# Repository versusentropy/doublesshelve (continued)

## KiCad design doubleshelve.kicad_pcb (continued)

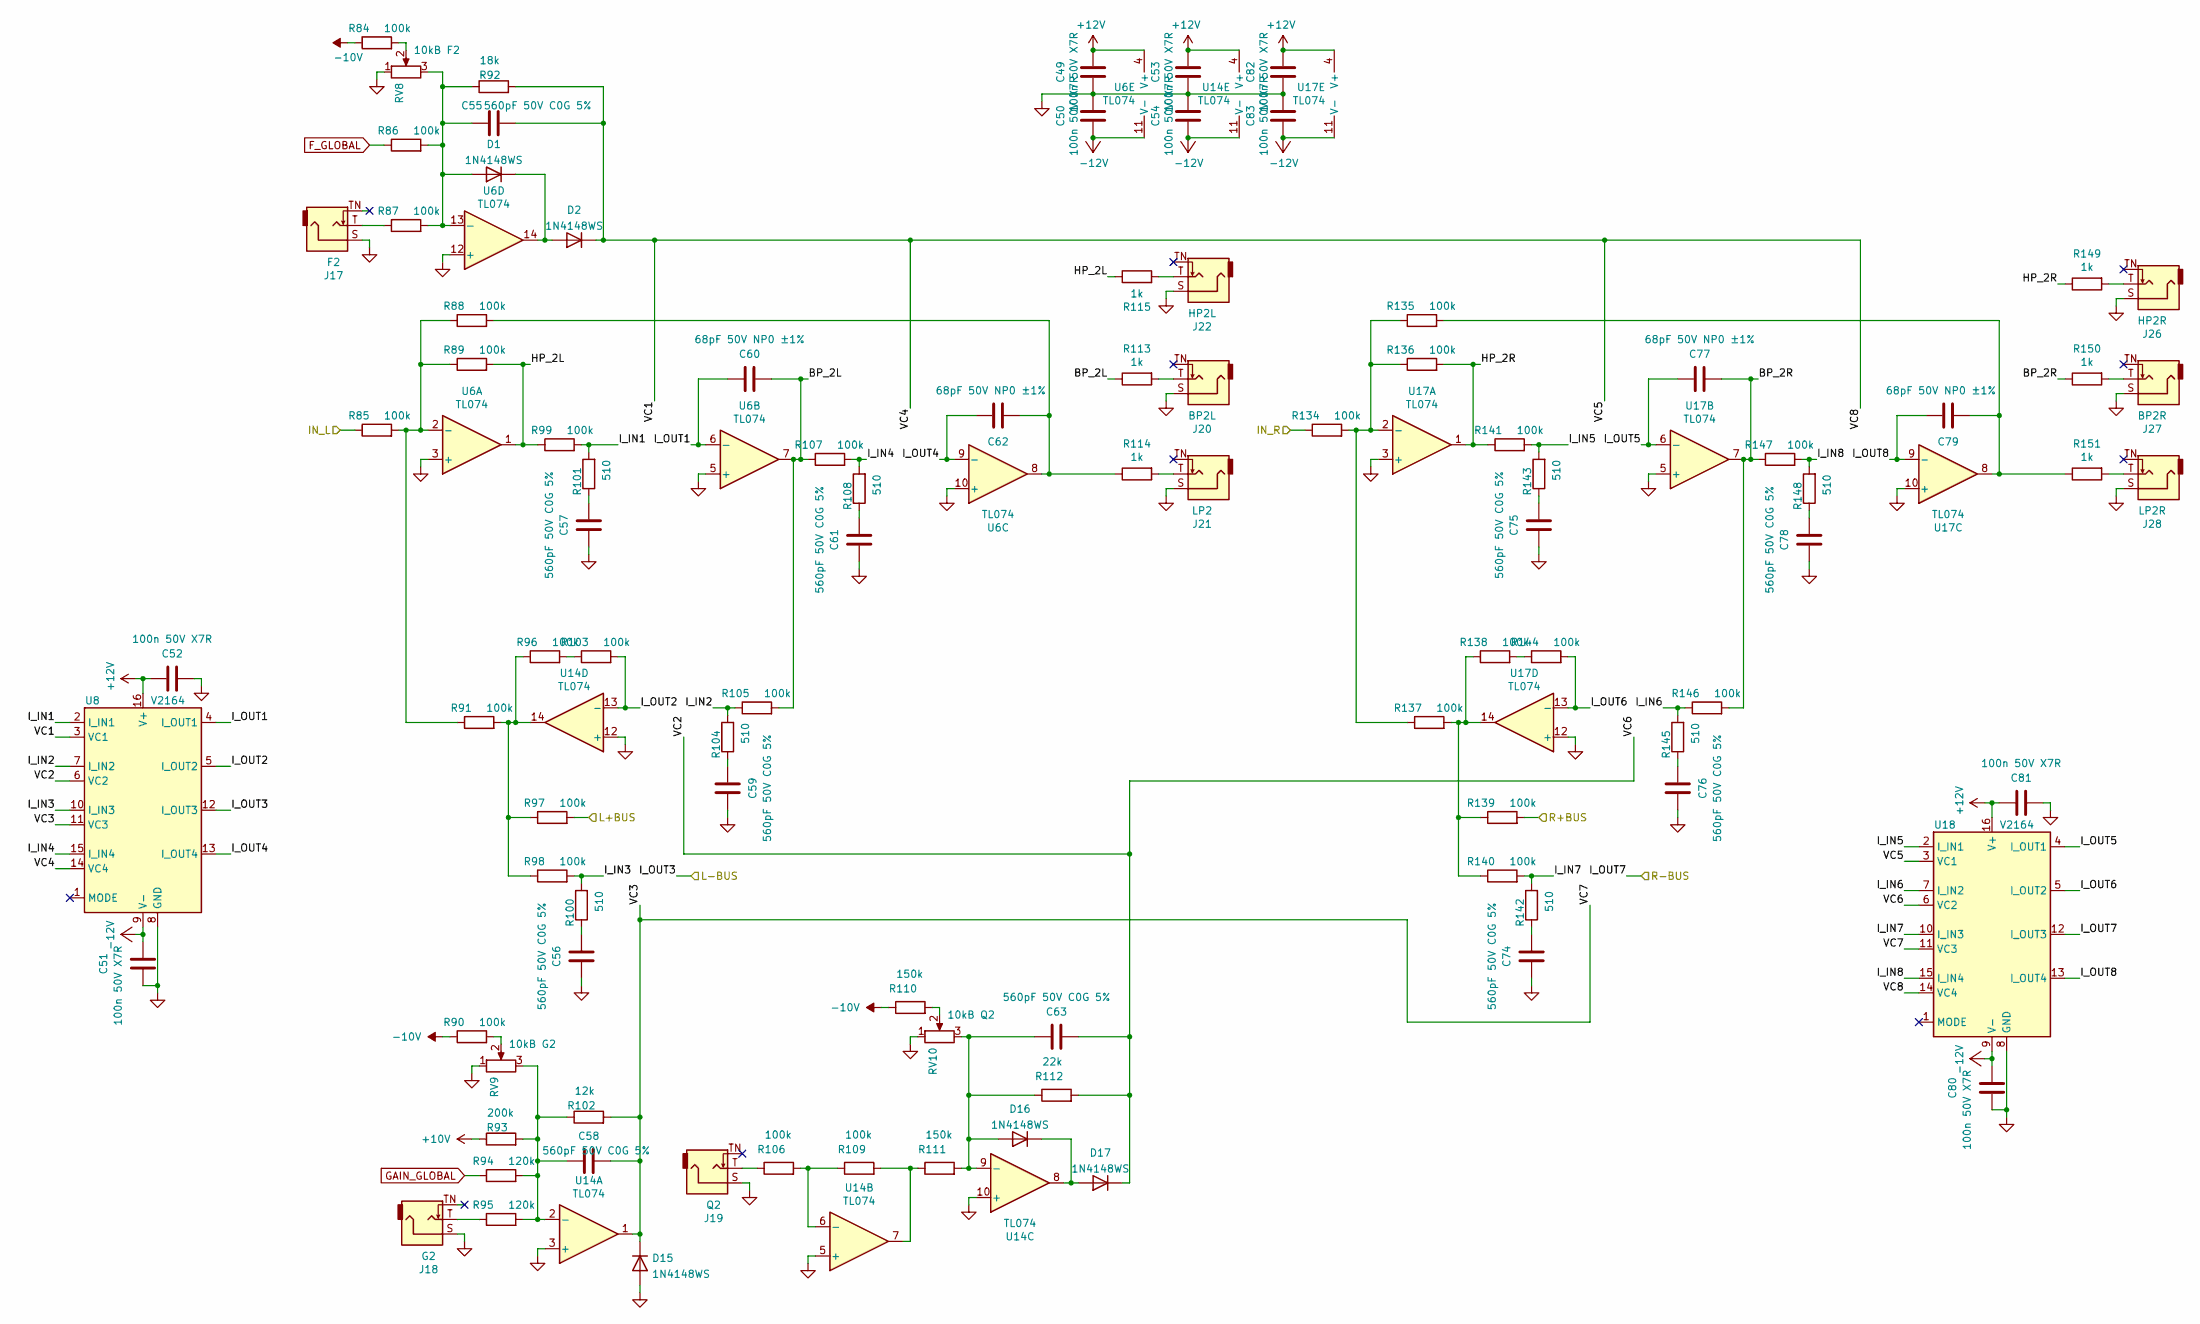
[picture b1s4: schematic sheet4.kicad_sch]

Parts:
C49, C50, C51, C52, C53, C54, C80, C81, C82, C83: 100n 50V X7R; C_0402_1005Metric; LCSC C307331
C55, C56, C57, C58, C59, C61, C63, C74, C75, C76, C78: 560pF 50V C0G 5%; C_0603_1608Metric; LCSC C97881
C60, C62, C77, C79: 68pF 50V NP0 ±1%; C_0402_1005Metric; LCSC C5182453
D1, D2, D15, D16, D17: 1N4148WS; D_SOD-323; LCSC C2128
J17: F2; Jack_3.5mm_QingPu_WQP-PJ398SM_Vertical_CircularHolesSMALL
J18: G2; Jack_3.5mm_QingPu_WQP-PJ398SM_Vertical_CircularHolesSMALL
J19: Q2; Jack_3.5mm_QingPu_WQP-PJ398SM_Vertical_CircularHolesSMALL
J20: BP2L; Jack_3.5mm_QingPu_WQP-PJ398SM_Vertical_CircularHolesSMALL
J21: LP2; Jack_3.5mm_QingPu_WQP-PJ398SM_Vertical_CircularHolesSMALL
J22: HP2L; Jack_3.5mm_QingPu_WQP-PJ398SM_Vertical_CircularHolesSMALL
J26: HP2R; Jack_3.5mm_QingPu_WQP-PJ398SM_Vertical_CircularHolesSMALL
J27: BP2R; Jack_3.5mm_QingPu_WQP-PJ398SM_Vertical_CircularHolesSMALL
J28: LP2R; Jack_3.5mm_QingPu_WQP-PJ398SM_Vertical_CircularHolesSMALL
R84, R85, R86, R87, R88, R89, R90, R91, R96, R97, R98, R99, R103, R105, R106, R107, R109, R134, R135, R136, R137, R138, R139, R140, R141, R144, R146, R147: 100k; R_0402_1005Metric; LCSC C319963
R92: 18k; R_0402_1005Metric
R93: 200k; R_0402_1005Metric
R94, R95: 120k; R_0402_1005Metric
R100, R101, R104, R108, R142, R143, R145, R148: 510; R_0402_1005Metric
R102: 12k; R_0402_1005Metric
R110, R111: 150k; R_0402_1005Metric
R112: 22k; R_0402_1005Metric
R113, R114, R115, R149, R150, R151: 1k; R_0603_1608Metric; LCSC C394536
RV8: 10kB F2; RD901F-ALPHA-POT
RV9: 10kB G2; RD901F-ALPHA-POT
RV10: 10kB Q2; RD901F-ALPHA-POT
U6, U14, U17: TL074; SOIC-14_3.9x8.7mm_P1.27mm; LCSC C96507
U8, U18: V2164; SOIC-16_3.9x9.9mm_P1.27mm

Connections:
+10V: R93.1; also elsewhere on the board
+12V: C49.2, C52.2, C53.2, C81.2, C82.2, U6.4 (V+), U8.16 (V+), U14.4 (V+), U17.4 (V+), U18.16 (V+); also elsewhere on the board
-10V: R84.1, R90.1, R110.1; also elsewhere on the board
-12V: C50.1, C51.2, C54.1, C80.2, C83.1, U6.11 (V-), U8.9 (V-), U14.11 (V-), U17.11 (V-), U18.9 (V-); also elsewhere on the board
/sheet1/IN_L: R85.1; also elsewhere on the board
/sheet1/IN_R: R134.1; also elsewhere on the board
/sheet1/L+BUS: R97.2; also elsewhere on the board
/sheet1/R+BUS: R139.2; also elsewhere on the board
/sheet3/I_OUT3: U8.12 (I_OUT3); also elsewhere on the board
/sheet3/I_OUT7: U18.12 (I_OUT3); also elsewhere on the board
/sheet4/BP_2L: C60.1, R105.2, R107.1, R113.1, U6.7
/sheet4/BP_2R: C77.1, R146.2, R147.1, R150.1, U17.7
/sheet4/HP_2L: R89.2, R99.1, R115.1, U6.1
/sheet4/HP_2R: R136.2, R141.1, R149.1, U17.1
/sheet4/I_IN1: R99.2, R101.2, U8.2 (I_IN1)
/sheet4/I_IN2: R104.2, R105.1, U8.7 (I_IN2)
/sheet4/I_IN3: R98.2, R100.2, U8.10 (I_IN3)
/sheet4/I_IN4: R107.2, R108.2, U8.15 (I_IN4)
/sheet4/I_IN5: R141.2, R143.2, U18.2 (I_IN1)
/sheet4/I_IN6: R145.2, R146.1, U18.7 (I_IN2)
/sheet4/I_IN7: R140.2, R142.2, U18.10 (I_IN3)
/sheet4/I_IN8: R147.2, R148.2, U18.15 (I_IN4)
/sheet4/I_OUT1: C60.2, U6.6 (-), U8.4 (I_OUT1)
/sheet4/I_OUT2: R103.2, U8.5 (I_OUT2), U14.13 (-)
/sheet4/I_OUT4: C62.2, U6.9 (-), U8.13 (I_OUT4)
/sheet4/I_OUT5: C77.2, U17.6 (-), U18.4 (I_OUT1)
/sheet4/I_OUT6: R144.2, U17.13 (-), U18.5 (I_OUT2)
/sheet4/I_OUT8: C79.2, U17.9 (-), U18.13 (I_OUT4)
/sheet4/VC1: C55.1, D2.1 (K), R92.2, U8.3 (VC1), U8.14 (VC4), U18.3 (VC1), U18.14 (VC4)
/sheet4/VC2: C63.1, D17.1 (K), R112.2, U8.6 (VC2), U18.6 (VC2)
/sheet4/VC3: C58.1, D15.1 (K), R102.2, U8.11 (VC3), U14.1, U18.11 (VC3)
F_GLOBAL: R86.1; also elsewhere on the board
GAIN_GLOBAL: R94.1; also elsewhere on the board
GNDA: C49.1, C50.2, C51.1, C52.1, C53.1, C54.2, C56.2, C57.2, C59.2, C61.2, C74.2, C75.2, C76.2, C78.2, C80.1, C81.1, C82.1, C83.2, D15.2 (A), J17.S, J18.S, J19.S, J20.S, J21.S, J22.S, J26.S, J27.S, J28.S, RV8.1, RV9.1, RV10.1, U6.3 (+), U6.5 (+), U6.10 (+), U6.12 (+), U8.8 (GND), U14.3 (+), U14.5 (+), U14.10 (+), U14.12 (+), U17.3 (+), U17.5 (+), U17.10 (+), U17.12 (+), U18.8 (GND); also elsewhere on the board
unnamed: C56.1, R100.1
unnamed: C57.1, R101.1
unnamed: C59.1, R104.1
unnamed: C61.1, R108.1
unnamed: C62.1, R88.2, R114.1, U6.8
unnamed: C74.1, R142.1
unnamed: C75.1, R143.1
unnamed: C76.1, R145.1
unnamed: C78.1, R148.1
unnamed: C79.1, R135.2, R151.1, U17.8
unnamed: C55.2, D1.2 (A), R86.2, R87.2, R92.1, RV8.3, U6.13 (-)
unnamed: D1.1 (K), D2.2 (A), U6.14
unnamed: C63.2, D16.2 (A), R111.2, R112.1, RV10.3, U14.9 (-)
unnamed: D16.1 (K), D17.2 (A), U14.8
unnamed: J17.T, R87.1
unnamed: J18.T, R95.1
unnamed: J19.T, R106.1
unnamed: J20.T, R113.2
unnamed: J21.T, R114.2
unnamed: J22.T, R115.2
unnamed: J26.T, R149.2
unnamed: J27.T, R150.2
unnamed: J28.T, R151.2
unnamed: R84.2, RV8.2
unnamed: R90.2, RV9.2
unnamed: R91.2, R96.1, R97.1, R98.1, U14.14
unnamed: R96.2, R103.1
unnamed: R109.2, R111.1, U14.7
unnamed: R110.2, RV10.2
unnamed: R137.2, R138.1, R139.1, R140.1, U17.14
unnamed: R138.2, R144.1
unnamed: R85.2, R88.1, R89.1, R91.1, U6.2 (-)
unnamed: C58.2, R93.2, R94.2, R95.2, R102.1, RV9.3, U14.2 (-)
unnamed: R106.2, R109.1, U14.6 (-)
unnamed: R134.2, R135.1, R136.1, R137.1, U17.2 (-)

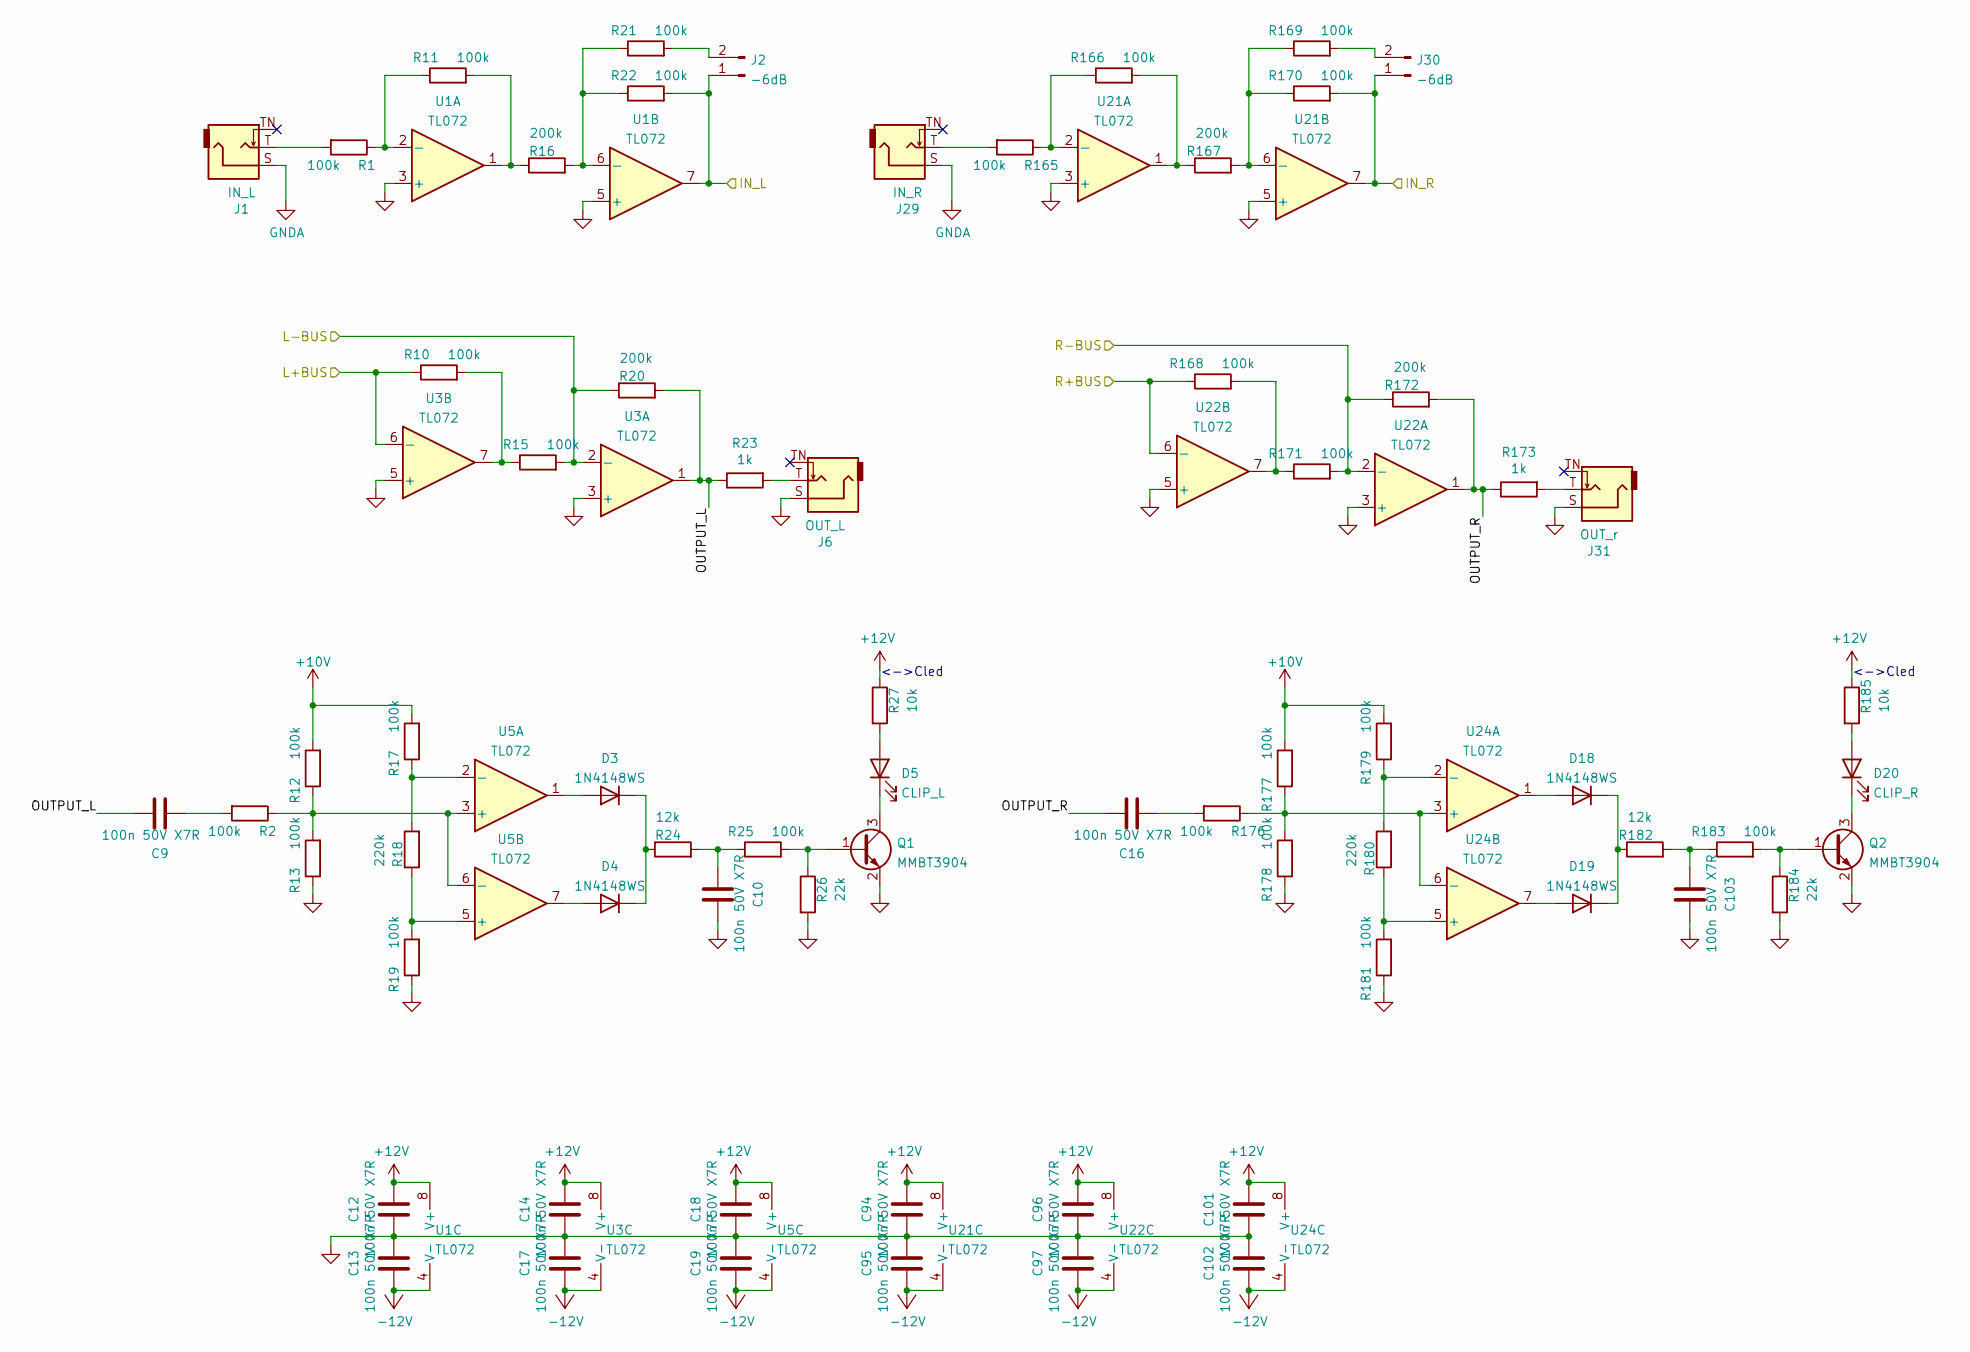
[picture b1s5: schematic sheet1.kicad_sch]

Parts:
C9, C10, C12, C13, C14, C16, C17, C18, C19, C94, C95, C96, C97, C101, C102, C103: 100n 50V X7R; C_0402_1005Metric; LCSC C307331
D3, D4, D18, D19: 1N4148WS; D_SOD-323; LCSC C2128
D5: CLIP_L; LED_D3.0mm
D20: CLIP_R; LED_D3.0mm
J1: IN_L; Jack_3.5mm_QingPu_WQP-PJ398SM_Vertical_CircularHolesSMALL
J2, J30: -6dB; PinHeader_1x02_P2.54mm_Vertical
J6: OUT_L; Jack_3.5mm_QingPu_WQP-PJ398SM_Vertical_CircularHolesSMALL
J29: IN_R; Jack_3.5mm_QingPu_WQP-PJ398SM_Vertical_CircularHolesSMALL
J31: OUT_r; Jack_3.5mm_QingPu_WQP-PJ398SM_Vertical_CircularHolesSMALL
Q1, Q2: MMBT3904; SOT-23; LCSC C20526
R1, R2, R10, R11, R12, R13, R15, R17, R19, R21, R22, R25, R165, R166, R168, R169, R170, R171, R176, R177, R178, R179, R181, R183: 100k; R_0402_1005Metric; LCSC C319963
R16, R20, R167, R172: 200k; R_0402_1005Metric
R18, R180: 220k; R_0402_1005Metric
R23, R173: 1k; R_0603_1608Metric; LCSC C394536
R24, R182: 12k; R_0402_1005Metric
R26, R184: 22k; R_0402_1005Metric
R27, R185: 10k; R_0402_1005Metric
U1, U3, U5, U21, U22, U24: TL072; SOIC-8_3.9x4.9mm_P1.27mm

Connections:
+10V: R12.2, R17.2, R177.2, R179.2; also elsewhere on the board
+12V: C12.2, C14.2, C18.2, C94.2, C96.2, C101.2, R27.1, R185.1, U1.8 (V+), U3.8 (V+), U5.8 (V+), U21.8 (V+), U22.8 (V+), U24.8 (V+); also elsewhere on the board
-12V: C13.1, C17.1, C19.1, C95.1, C97.1, C102.1, U1.4 (V-), U3.4 (V-), U5.4 (V-), U21.4 (V-), U22.4 (V-), U24.4 (V-); also elsewhere on the board
/sheet1/IN_L: J2.1, R22.2, U1.7; also elsewhere on the board
/sheet1/IN_R: J30.1, R170.2, U21.7; also elsewhere on the board
/sheet1/L+BUS: R10.1, U3.6 (-); also elsewhere on the board
/sheet1/OUTPUT_L: C9.2, R20.2, R23.1, U3.1
/sheet1/OUTPUT_R: C16.2, R172.2, R173.1, U22.1
/sheet1/R+BUS: R168.1, U22.6 (-); also elsewhere on the board
/sheet3/I_OUT3: R15.2, R20.1, U3.2 (-); also elsewhere on the board
/sheet3/I_OUT7: R171.2, R172.1, U22.2 (-); also elsewhere on the board
GNDA: C10.2, C12.1, C13.2, C14.1, C17.2, C18.1, C19.2, C94.1, C95.2, C96.1, C97.2, C101.1, C102.2, C103.2, J1.S, J6.S, J29.S, J31.S, Q1.2 (E), Q2.2 (E), R13.1, R19.1, R26.2, R178.1, R181.1, R184.2, U1.3 (+), U1.5 (+), U3.3 (+), U3.5 (+), U21.3 (+), U21.5 (+), U22.3 (+), U22.5 (+); also elsewhere on the board
unnamed: C9.1, R2.2
unnamed: C10.1, R24.2, R25.1
unnamed: C16.1, R176.2
unnamed: C103.1, R182.2, R183.1
unnamed: D3.2 (A), U5.1
unnamed: D3.1 (K), D4.1 (K), R24.1
unnamed: D4.2 (A), U5.7
unnamed: D5.2 (A), R27.2
unnamed: D5.1 (K), Q1.3 (C)
unnamed: D18.2 (A), U24.1
unnamed: D18.1 (K), D19.1 (K), R182.1
unnamed: D19.2 (A), U24.7
unnamed: D20.2 (A), R185.2
unnamed: D20.1 (K), Q2.3 (C)
unnamed: J1.T, R1.2
unnamed: J2.2, R21.2
unnamed: J6.T, R23.2
unnamed: J29.T, R165.2
unnamed: J30.2, R169.2
unnamed: J31.T, R173.2
unnamed: Q1.1 (B), R25.2, R26.1
unnamed: Q2.1 (B), R183.2, R184.1
unnamed: R10.2, R15.1, U3.7
unnamed: R11.2, R16.1, U1.1
unnamed: R166.2, R167.1, U21.1
unnamed: R168.2, R171.1, U22.7
unnamed: R1.1, R11.1, U1.2 (-)
unnamed: R16.2, R21.1, R22.1, U1.6 (-)
unnamed: R2.1, R12.1, R13.2, U5.3 (+), U5.6 (-)
unnamed: R17.1, R18.2, U5.2 (-)
unnamed: R18.1, R19.2, U5.5 (+)
unnamed: R165.1, R166.1, U21.2 (-)
unnamed: R167.2, R169.1, R170.1, U21.6 (-)
unnamed: R176.1, R177.1, R178.2, U24.3 (+), U24.6 (-)
unnamed: R179.1, R180.2, U24.2 (-)
unnamed: R180.1, R181.2, U24.5 (+)

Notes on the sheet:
<->Cled

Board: 2 copper layers, 375 parts (335 on the bottom side), 207 nets, no tracks yet.

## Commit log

2023-10-19 init
